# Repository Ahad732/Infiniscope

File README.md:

# infiniscope

Infiniscope is a custom 12-bit oscilloscope made with the RP2350, and the AD9238BSTRL ADC. It is made on a 4-layer stackup with sig-gnd-pwr-sig as the stackup. it has a BNC connector which can be used to attach a probe and measure signals. There are 3 options that are selectable, time divison, gain and ac/dc coupling, which helps in measuring different kinds of signals. the basic test firmware for this O-scope can be found [here](https://github.com/Keyaan-07/scope-fw) written by yours truly(Keyaan). The firmware is custom written in C and can be modified easily according to user needs. There is an optional display for the display, but it hasn't been showin in this instance. 

check the PCB on [KiCanvas](https://kicanvas.org/?repo=https%3A%2F%2Fgithub.com%2FAhad732%2FInfiniscope%2Ftree%2Fmain%2FHardware)!  
Check the 3d model in Onshape [here](https://cad.onshape.com/documents/e5e2611525100d0b74de0cef/w/a750fed0a475cfc636f591fd/e/fb3ff11a8c4d4a0d7b13289f)  

# Contributors
Ahad and Keyaan, 
Made for [Hack Club](https://hackclub.com/) [ThirdSpace](https://thirdspace.hackclub.com/)!!

# LICENSE
Licensed under the MIT License

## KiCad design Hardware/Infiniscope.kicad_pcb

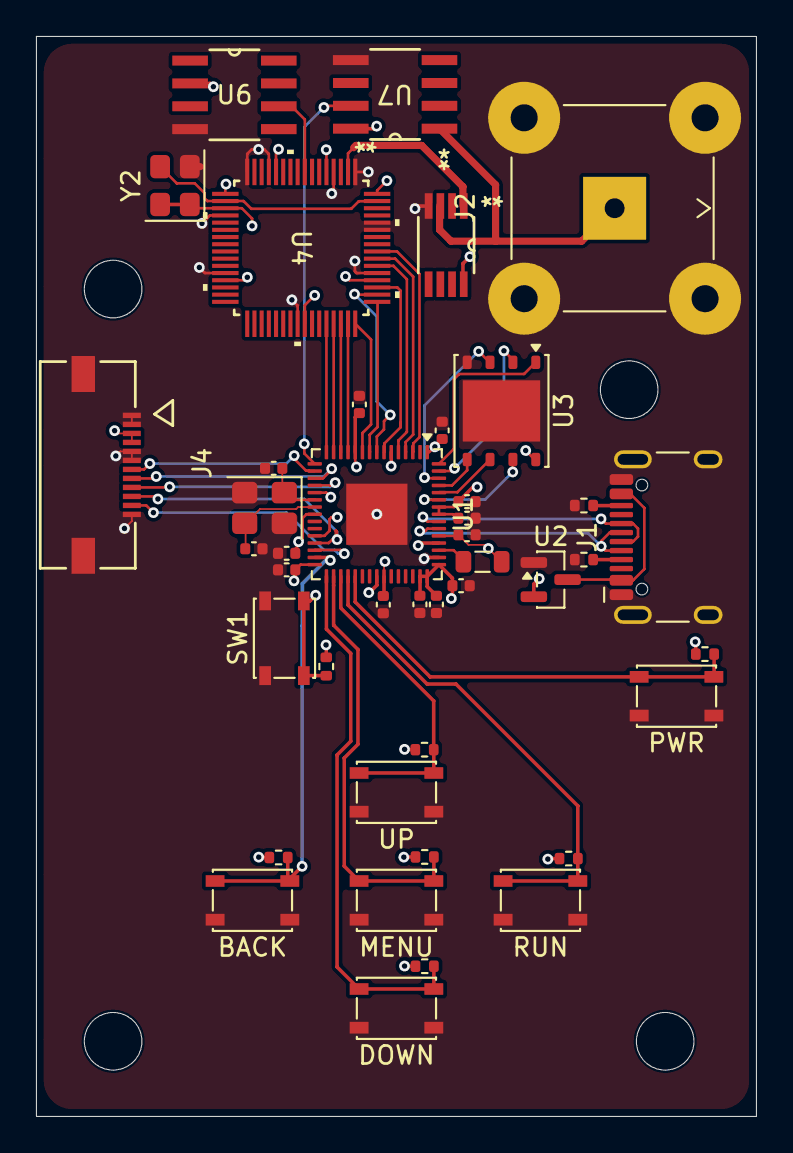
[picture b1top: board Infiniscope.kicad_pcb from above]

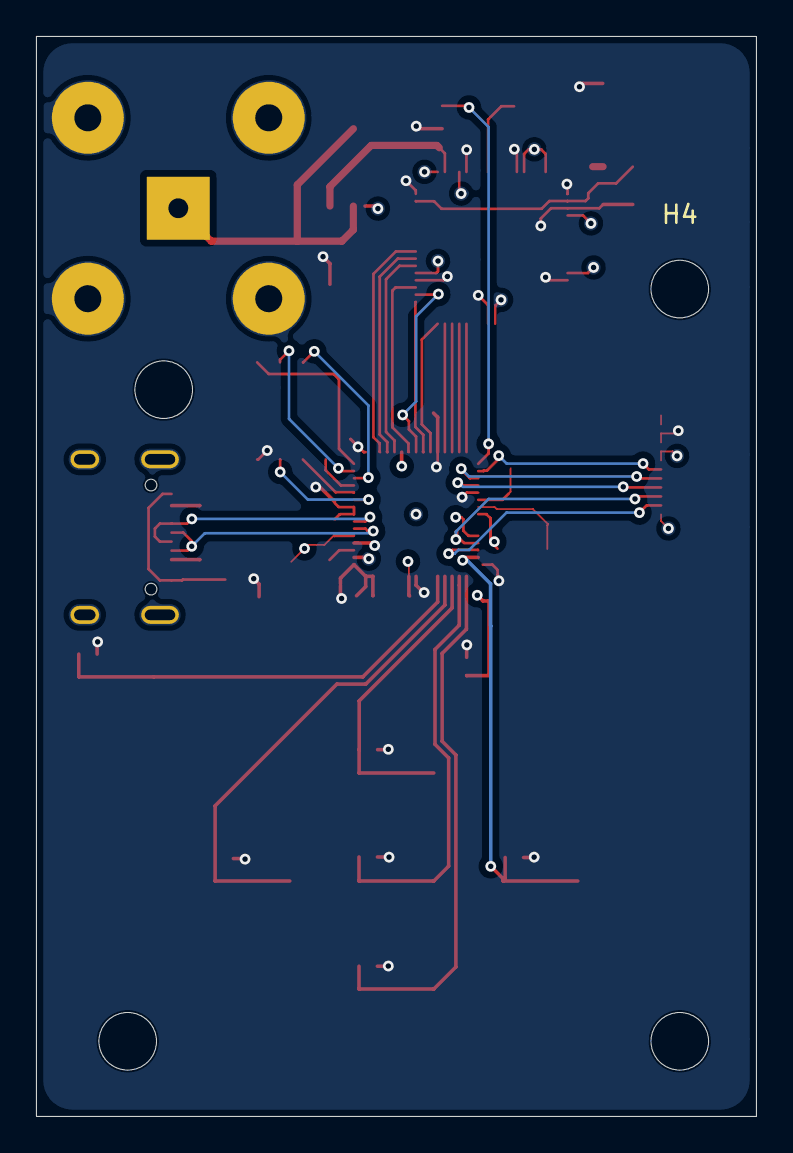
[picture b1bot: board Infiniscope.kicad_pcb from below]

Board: 4 copper layers, 40.0 x 60.0 mm, 46 parts (4 on the bottom side), 45 nets.

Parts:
BACK: SW_Push; SW_SPST_PTS810
C1, C2: 15pf; C_0402_1005Metric
C3, C4, C5, C6, C7, C8, C9, C10, C11, C12, C14: 100n; C_0402_1005Metric
DOWN: SW_Push; SW_SPST_PTS810
H1, H2, H3, H4: MountingHole; MountingHole_3.2mm_M3
J1: USB_C_Receptacle_USB2.0_16P; USB_C_Receptacle_HCTL_HC-TYPE-C-16P-01A
J2: Conn_Coaxial; BNC_TEConnectivity_1478035_Horizontal
J4: 5051101297; CON_5051101297_MOL
L1: 3.3u; L_0805_2012Metric
MENU: SW_Push; SW_SPST_PTS810
PWR: SW_Push; SW_SPST_PTS810
R1, R2: 5.1k; R_0402_1005Metric
R3, R4, R5, R6, R7, R8, R9: 10K; R_0402_1005Metric
RUN: SW_Push; SW_SPST_PTS810
SW1: SW_Push; SW_SPST_PTS810
U1: RP2350A; QFN-60-1EP_7x7mm_P0.4mm_EP3.4x3.4mm
U2: MCP1700x-330xxTT; SOT-23
U3: W25Q128JVP; WSON-8-1EP_6x5mm_P1.27mm_EP3.4x4.3mm
U4: AD9238BSTRL-65; ST_64_1_ADI
U5: OPA2320AIDGKR; DGK8
U6: REF5025ID; D8
U7: TLV3502AIDR; D8
UP: SW_Push; SW_SPST_PTS810
Y1: Crystal_GND24; Crystal_SMD_3225-4Pin_3.2x2.5mm
Y2: 10 mhz cmos oscillator; Oscillator_SMD_Abracon_ASE-4Pin_3.2x2.5mm

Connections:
+1V1: C10.1, C11.1, C12.1, L1.2, U1.6 (DVDD), U1.23 (DVDD), U1.39 (DVDD), U1.50 (VREG_FB)
+3V3: C3.1, C4.1, C5.1, C6.1, C7.1, C8.1, C9.1, C14.1, J4.3, J4.4, R3.1, R4.1, R5.1, R6.1, R7.1, R8.1, R9.1, U1.1 (IOVDD), U1.11 (IOVDD), U1.20 (IOVDD), U1.30 (IOVDD), U1.38 (IOVDD), U1.44 (ADC_AVDD), U1.45 (IOVDD), U1.46 (VREG_AVDD), U1.49 (VREG_VIN), U1.53 (USB_OTP_VDD), U1.54 (QSPI_IOVDD), U2.2 (VO), U3.8 (VCC), U4.5 (AVDD), U4.12 (AVDD), U4.17 (AVDD), U4.19 (DCS), U4.29 (DRVDD), U4.41 (DRVDD), U4.52 (DRVDD), U4.64 (AVDD), U5.8 (V+), U6.2 (VIN), U7.8 (V+), Y2.1 (EN), Y2.4 (Vdd)
/ADC_CLK: U4.18 (CLK_B), U4.63 (CLK_A), Y2.3 (OUT)
/ADC_VREF: U4.8 (VREF), U6.6 (VOUT)
/BTN_BACK: BACK.2, R5.2, U1.29 (GPIO18)
/BTN_DOWN: DOWN.2, R8.2, U1.31 (GPIO19)
/BTN_MENU: MENU.2, R6.2, U1.32 (GPIO20)
/BTN_PWR: PWR.2, R4.2, U1.35 (GPIO23)
/BTN_RUN: R7.2, RUN.2, U1.34 (GPIO22)
/BTN_UP: R9.2, U1.33 (GPIO21), UP.2
/CS: J4.8, U1.18 (GPIO14)
/DATA+: J1.A6 (D+), J1.B6 (D+), U1.52 (USB_DP)
/DATA-: J1.A7 (D-), J1.B7 (D-), U1.51 (USB_DM)
/D/C: J4.7, U1.17 (GPIO13)
/GP1: U1.3 (GPIO1), U4.56 (D10_A)
/GP2: U1.4 (GPIO2), U4.55 (D9_A)
/GP3: U1.5 (GPIO3), U4.54 (D8_A)
/GP4: U1.7 (GPIO4), U4.51 (D7_A)
/GP5: U1.8 (GPIO5), U4.50 (D6_A)
/GP6: U1.9 (GPIO6), U4.49 (D5_A)
/GP7: U1.10 (GPIO7), U4.48 (D4_A)
/GP8: U1.12 (GPIO8), U4.47 (D3_A)
/GP9: U1.13 (GPIO9), U4.46 (D2_A)
/GP10: U1.14 (GPIO10), U4.45 (D1_A)
/GP11: U1.15 (GPIO11), U4.44 (D0_A)
/GP12: U1.16 (GPIO12), U7.7 (OUTA)
/IN1+: J2.1 (In), U5.3 (INA+), U7.1 (INA+)
/OUTA: U4.2 (VIN+_A), U5.1 (OUTA)
/QSPI_CLK: U1.56 (QSPI_SCLK), U3.6 (CLK)
/QSPI_CS: U1.60 (~QSPI_SS), U3.1 (~CS)
/QSPI_IO0: U1.57 (QSPI_SD0), U3.5 (DI/IO_{0})
/QSPI_IO1: U1.59 (QSPI_SD1), U3.2 (DO/IO_{1})
/QSPI_IO2: U1.58 (QSPI_SD2), U3.3 (~WP/IO_{2})
/QSPI_IO3: U1.55 (QSPI_SD3), U3.7 (~HOLD/~RESET/IO_{3})
/RESET: J4.11, U1.28 (GPIO17)
/RUN: R3.2, SW1.2, U1.26 (RUN)
/SCL: J4.9, U1.19 (GPIO15)
/SDA: J4.10, U1.27 (GPIO16)
/XIN: C2.1, U1.21 (XIN), Y1.1
/XOUT: C1.1, U1.22 (XOUT), Y1.3
GND: BACK.1, C1.2, C2.2, C3.2, C4.2, C5.2, C6.2, C7.2, C8.2, C9.2, C10.2, C11.2, C12.2, C14.2, DOWN.1, J1.A1 (GND), J1.A12 (GND), J1.B1 (GND), J1.B12 (GND), J1.SH (SHIELD), J2.2 (Ext), J4.1, J4.2, J4.5, J4.6, J4.12, J4.P1, J4.P2, MENU.1, PWR.1, R1.2, R2.2, RUN.1, SW1.1, U1.47 (VREG_PGND), U1.61 (GND), U2.1 (GND), U3.4 (GND), U3.9 (EP), U4.1 (AGND), U4.4 (AGND), U4.13 (AGND), U4.16 (AGND), U4.20 (DFS), U4.28 (DRGND), U4.40 (DRGND), U4.53 (DRGND), U4.59 (OEB_A), U4.60 (PDWN_A), U5.4 (V-), U6.4 (GND), U7.5 (V-), UP.1, Y1.2 (G), Y1.4 (G), Y2.2 (GND)
unnamed: J1.A5 (CC1), R1.1
unnamed: J1.B5 (CC2), R2.1
unnamed: L1.1, U1.48 (VREG_LX)
VBUS: J1.A4 (VBUS), J1.A9 (VBUS), J1.B4 (VBUS), J1.B9 (VBUS), U2.3 (VI)

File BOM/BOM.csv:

Designator,Footprint,Value,Quantity,Price,Link
"BACK, DOWN, MENU, PWR, RUN, SW1, UP",SW_SPST_PTS810,SW_Push,10,3.43,https://www.lcsc.com/product-detail/C221895.html
"C1, C2",402,15pf,50,0.08,https://www.lcsc.com/product-detail/C696887.html
"C10, C11, C12, C14, C3, C4, C5, C6, C7, C8, C9",402,100n,100,0.14,https://www.lcsc.com/product-detail/C285038.html
J1,USB_C_Receptacle_HCTL_HC-TYPE-C-16P-01A,USB_C_Receptacle_USB2.0_16P,10,0.53,https://www.lcsc.com/product-detail/C42400252.html
J2,BNC_TEConnectivity_1478035_Horizontal,Conn_Coaxial,3,8.47,https://robu.in/product/smb-rf-coax-angled-through-hole-male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
J4,CON_5051101297_MOL,12 Pin FFC P 1mm,5,0.62,https://www.lcsc.com/product-detail/C22371030.html?
L1,805,3.3u,20,0.44,https://www.lcsc.com/product-detail/C2926398.html
"R1, R2",402,5.1k,100,0.07,https://www.lcsc.com/product-detail/C54920691.html
"R3, R4, R5, R6, R7, R8, R9",402,10K,100,0.09,https://www.lcsc.com/product-detail/C2759773.html
U1,QFN-60-1EP_7x7mm_P0.4mm_EP3.4x3.4mm,RP2350A,3,3.9,https://www.lcsc.com/product-detail/C42411118.html
U2,SOT-23,MCP1700x-330xxTT,5,0.55,https://www.lcsc.com/product-detail/C41381676.html
U3,WSON-8-1EP_6x5mm_P1.27mm_EP3.4x4.3mm,W25Q128JVP,3,11.14,https://www.lcsc.com/product-detail/C190862.html
U4,ST_64_1_ADI,AD9238BSTRL-65,1,27.48,https://www.lioncircuits.com/parts/AD9288BSTZ-40
U5,DGK8,OPA2320AIDGKR,1,16.99,https://www.lcsc.com/product-detail/C545235.html?
U6,D8,REF5025ID,2,7.01,https://www.lcsc.com/product-detail/C523999.html
U7,D8,TLV3502AIDR,3,6.21,https://www.lcsc.com/product-detail/C131165.html
Y1,Crystal_SMD_3225-4Pin_3.2x2.5mm,12 mhz,10,0.55,https://www.lcsc.com/product-detail/C16197268.html
Y2,Oscillator_SMD_Abracon_ASE-4Pin_3.2x2.5mm,10 mhz cmos oscillator,5,1.3,https://www.lcsc.com/product-detail/C49329945.html
,,PCB+stencil,,22.35,
,,Screen,1,3.25,https://robu.in/product/goldenmorning-st7789v-240x320-spi-2-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
,,TOTAL,,114.6,
